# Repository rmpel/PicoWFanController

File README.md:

# PicoFanController

A small, quiet controller for a standard 4-wire PC fan, built around a
Raspberry Pi Pico W. Designed for dual duty: solder-fume extractor on the
bench, bedroom fan at night.

Control is by rotary encoder + push-button on the device itself, or over
WiFi via a built-in web UI and REST API. A 10-segment LED bar shows the
current speed at a glance.

## Features

- 25 kHz PWM drive, tachometer read-back, configurable PWM polarity
- Rotary encoder with short-press, double-click and press-and-hold gestures
- Predefined / boost / min speeds, configurable step size
- 10-LED bar graph for speed, also used as WiFi-status indicator at boot
- WiFi client with AP fallback and captive-portal-style setup page
- REST API + responsive web UI (main + advanced settings pages)
- Settings persisted in on-device json storage

## Repository layout

- [`Firmware/`](Firmware/README.md) — MicroPython firmware, web UI, install/deploy scripts
- [`HARDWARE.md`](HARDWARE.md) — schematic, PCB and bill of materials
- `PicoFanController.kicad_*` — KiCad 9 project files

## Getting started

1. Build or assemble the hardware — see [HARDWARE.md](HARDWARE.md).
2. Flash and configure the firmware — see [Firmware/README.md](Firmware/README.md).

## License

The repo is split into two licenses, both noncommercial, both requiring
attribution:

- **Firmware and web UI** (`Firmware/`) — [PolyForm Noncommercial 1.0.0](Firmware/LICENSE).
  A software-specific noncommercial license.
- **Hardware design** (schematic, PCB, `HARDWARE.md`) —
  [CC BY-NC-SA 4.0](LICENSE-HARDWARE). Attribution, noncommercial, share-alike.

In short: do what you like with it for personal, educational or hobby use,
credit the author, and share improvements under the same terms. For
commercial use or anything that would involve claiming ownership, contact
me first.

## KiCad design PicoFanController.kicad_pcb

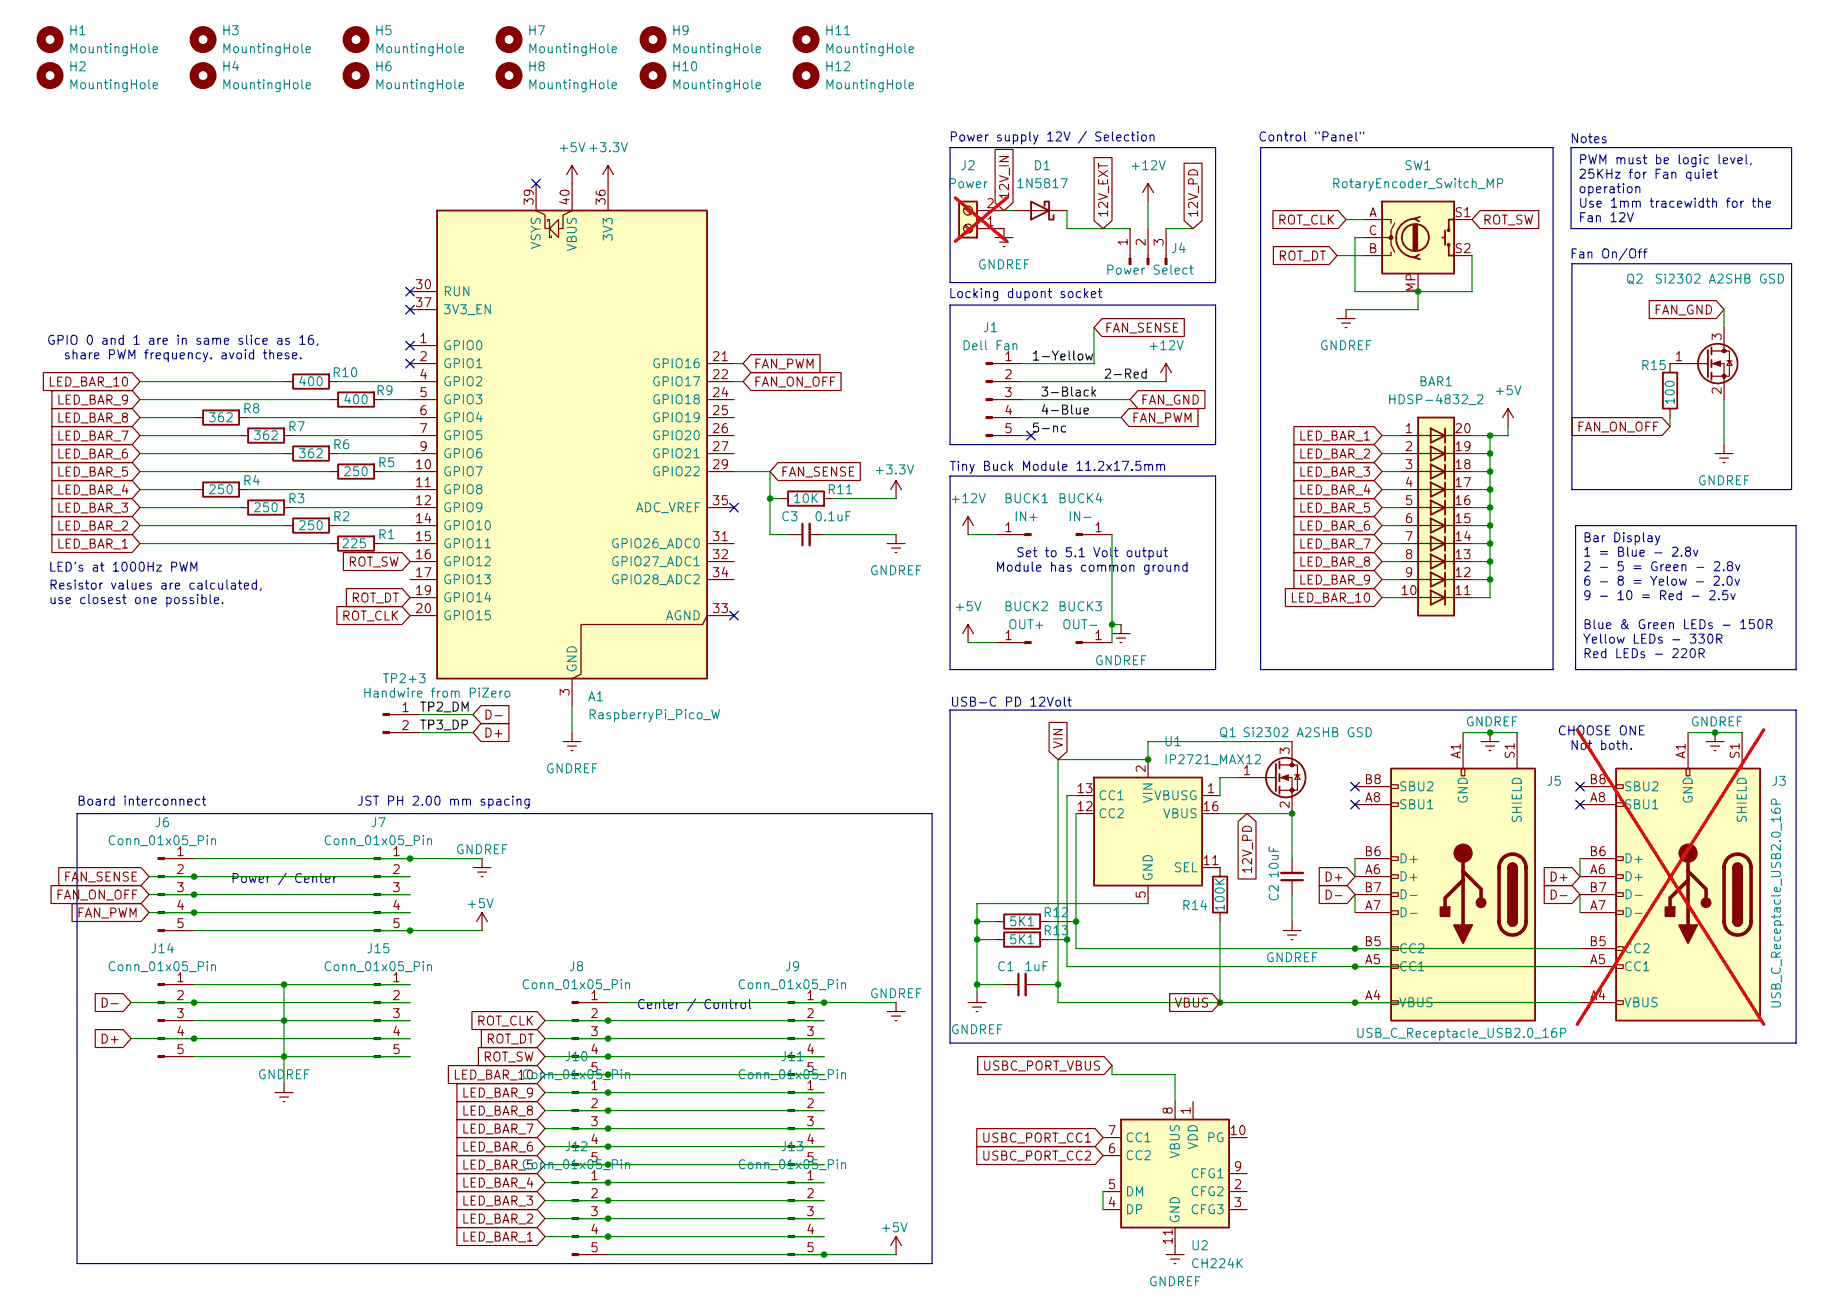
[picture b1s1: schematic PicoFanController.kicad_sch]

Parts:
A1: RaspberryPi_Pico_W; RaspberryPi_Pico_Common_THT
BAR1: HDSP-4832_2; HDSP-4832
BUCK1: IN+; SolderWire-0.75sqmm_1x01_D1.25mm_OD2.3mm
BUCK2: OUT+; SolderWire-0.75sqmm_1x01_D1.25mm_OD2.3mm
BUCK3: OUT-; SolderWire-0.75sqmm_1x01_D1.25mm_OD2.3mm
BUCK4: IN-; SolderWire-0.75sqmm_1x01_D1.25mm_OD2.3mm
C1: 1uF; C_0603_1608Metric_Pad1.08x0.95mm_HandSolder
C2: 10uF; C_0603_1608Metric_Pad1.08x0.95mm_HandSolder
C3: 0.1uF; C_0603_1608Metric_Pad1.08x0.95mm_HandSolder
D1: 1N5817; D_DO-15_P10.16mm_Horizontal
H1, H2, H3, H4, H5, H6, H7, H8, H9, H10, H11, H12: MountingHole; MountingHole_3.2mm_M3_DIN965
J1: Dell Fan; PinHeader_1x05_P2.54mm_Horizontal
J2: Power; TerminalBlock_Phoenix_MKDS-3-2-5.08_1x02_P5.08mm_Horizontal; not fitted
J3: USB_C_Receptacle_USB2.0_16P; USB_C_Receptacle_GCT_USB4105-xx-A_16P_TopMnt_Horizontal; not fitted
J4: Power Select; PinHeader_1x03_P2.54mm_Vertical
J5: USB_C_Receptacle_USB2.0_16P; USB_C_Receptacle_G-Switch_GT-USB-7051x
J6, J7, J8, J9, J10, J11, J12, J13, J14, J15: Conn_01x05_Pin; JST_PH_B5B-PH-K_1x05_P2.00mm_Vertical
Q1, Q2: Si2302 A2SHB GSD; SOT-23-3
R1: 225; R_0603_1608Metric_Pad0.98x0.95mm_HandSolder
R2, R3, R4, R5: 250; R_0603_1608Metric_Pad0.98x0.95mm_HandSolder
R6, R7, R8: 362; R_0603_1608Metric_Pad0.98x0.95mm_HandSolder
R9, R10: 400; R_0603_1608Metric_Pad0.98x0.95mm_HandSolder
R11: 10K; R_0603_1608Metric_Pad0.98x0.95mm_HandSolder
R12, R13: 5K1; R_0603_1608Metric_Pad0.98x0.95mm_HandSolder
R14: 100K; R_0603_1608Metric_Pad0.98x0.95mm_HandSolder
R15: 100; R_0603_1608Metric_Pad0.98x0.95mm_HandSolder
SW1: RotaryEncoder_Switch_MP; RotaryEncoder_Alps_EC11E-Switch_Vertical_H20mm
TP2+3: Handwire from PiZero; PinHeader_1x02_P2.54mm_Vertical
U1: IP2721_MAX12; TSSOP-16_4.4x5mm_P0.65mm
U2: CH224K; SSOP-10-1EP_3.9x4.9mm_P1mm_EP2.1x3.3mm

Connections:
12V_EXT: D1.1 (K), J4.1
12V_IN: D1.2 (A), J2.2
12V_PD: C2.2, J4.3, Q1.2 (S), U1.16 (VBUS)
+3.3V: A1.36 (3V3), R11.2
+5V: A1.40 (VBUS), BAR1.11 (K), BAR1.12 (K), BAR1.13 (K), BAR1.14 (K), BAR1.15 (K), BAR1.16 (K), BAR1.17 (K), BAR1.18 (K), BAR1.19 (K), BAR1.20 (K), BUCK2.1, J6.5, J7.5, J12.5, J13.5
+12V: BUCK1.1, J1.2, J4.2
/5-nc: J1.5
D+: J3.A6 (D+), J3.B6 (D+), J5.A6 (D+), J5.B6 (D+), J14.4, J15.4, TP2+3.2
D-: J3.A7 (D-), J3.B7 (D-), J5.A7 (D-), J5.B7 (D-), J14.2, J15.2, TP2+3.1
FAN_GND: J1.3, Q2.3 (D)
FAN_ON_OFF: A1.22 (GPIO17), J6.3, J7.3, R15.1
FAN_PWM: A1.21 (GPIO16), J1.4, J6.4, J7.4
FAN_SENSE: A1.29 (GPIO22), C3.1, J1.1, J6.2, J7.2, R11.1
GNDREF: A1.3 (GND), A1.8 (GND), A1.13 (GND), A1.18 (GND), A1.23 (GND), A1.28 (GND), A1.38 (GND), BUCK3.1, BUCK4.1, C1.1, C2.1, C3.2, J2.1, J3.A1 (GND), J3.A12 (GND), J3.B1 (GND), J3.B12 (GND), J3.S1 (SHIELD), J5.A1 (GND), J5.A12 (GND), J5.B1 (GND), J5.B12 (GND), J5.S1 (SHIELD), J6.1, J7.1, J8.1, J9.1, J14.1, J14.3, J14.5, J15.1, J15.3, J15.5, Q2.2 (S), R12.1, R13.1, SW1.C, SW1.MP, SW1.S2, U1.5 (GND), U2.11 (GND)
LED_BAR_1: BAR1.1 (A), J12.4, J13.4, R1.1
LED_BAR_2: BAR1.2 (A), J12.3, J13.3, R2.1
LED_BAR_3: BAR1.3 (A), J12.2, J13.2, R3.1
LED_BAR_4: BAR1.4 (A), J12.1, J13.1, R4.1
LED_BAR_5: BAR1.5 (A), J10.5, J11.5, R5.1
LED_BAR_6: BAR1.6 (A), J10.4, J11.4, R6.1
LED_BAR_7: BAR1.7 (A), J10.3, J11.3, R7.1
LED_BAR_8: BAR1.8 (A), J10.2, J11.2, R8.1
LED_BAR_9: BAR1.9 (A), J10.1, J11.1, R9.1
LED_BAR_10: BAR1.10 (A), J8.5, J9.5, R10.1
unnamed: A1.4 (GPIO2), R10.2
unnamed: A1.5 (GPIO3), R9.2
unnamed: A1.6 (GPIO4), R8.2
unnamed: A1.7 (GPIO5), R7.2
unnamed: A1.9 (GPIO6), R6.2
unnamed: A1.10 (GPIO7), R5.2
unnamed: A1.11 (GPIO8), R4.2
unnamed: A1.12 (GPIO9), R3.2
unnamed: A1.14 (GPIO10), R2.2
unnamed: A1.15 (GPIO11), R1.2
unnamed: J3.A5 (CC1), J5.A5 (CC1), R13.2, U1.13 (CC1)
unnamed: J3.B5 (CC2), J5.B5 (CC2), R12.2, U1.12 (CC2)
unnamed: Q1.1 (G), U1.1 (VBUSG)
unnamed: Q2.1 (G), R15.2
unnamed: R14.1, U1.11 (SEL)
unnamed: U2.4 (DP), U2.5 (DM)
ROT_CLK: A1.20 (GPIO15), J8.2, J9.2, SW1.A
ROT_DT: A1.19 (GPIO14), J8.3, J9.3, SW1.B
ROT_SW: A1.16 (GPIO12), J8.4, J9.4, SW1.S1
VBUS: C1.2, J3.A4 (VBUS), J3.A9 (VBUS), J3.B4 (VBUS), J3.B9 (VBUS), J5.A4 (VBUS), J5.A9 (VBUS), J5.B4 (VBUS), J5.B9 (VBUS), Q1.3 (D), R14.2, U1.2 (VIN)

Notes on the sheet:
Notes
Resistor values are calculated, use closest one possible.
Center / Control
Power / Center
USB-C PD 12Volt
JST PH 2.00 mm spacing
LED's at 1000Hz PWM
Set to 5.1 Volt output Module has common ground
Fan On/Off
CHOOSE ONE Not both.
Control "Panel"
GPIO 0 and 1 are in same slice as 16, share PWM frequency. avoid these.
Board interconnect
Tiny Buck Module 11.2x17.5mm
Power supply 12V / Selection
Locking dupont socket
PWM must be logic level, 25KHz for Fan quiet operation Use 1mm tracewidth for the Fan 12V
Bar Display 1 = Blue - 2.8v 2 - 5 = Green - 2.8v 6 - 8 = Yelow - 2.0v 9 - 10 = Red - 2.5v Blue & Green LEDs - 150R Yellow LEDs - 330R Red LEDs - 220R

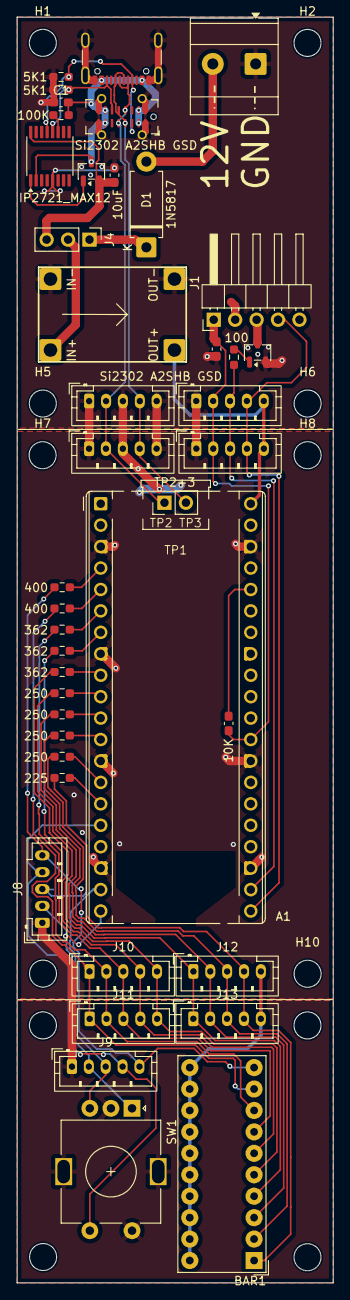
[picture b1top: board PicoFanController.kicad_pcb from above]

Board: 2 copper layers, 37.5 x 150.0 mm, 57 parts (0 on the bottom side), 42 nets.

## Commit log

2026-04-18 Firmware working, schematic on it's way, but the IC is hard to get, refactor to use CH224K
2026-04-18 Postponed the refactor
2026-04-19 first ledbar led now used for status during wifi for checking connection status, blinking is "connecting", SOS = failed to get wifi in 3 attempts, 5 second solid = WiFi connected. LED order is now co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
2026-04-19 Backups might be useful, might delete later, idk
2026-04-19 license and documentation
2026-04-28 Add wireless file management
